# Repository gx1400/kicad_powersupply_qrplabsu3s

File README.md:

# Linear regulator Power supply for QRP Labs Ultimate 3s

Designed in KiCad using NTE1929
PCB fab by OshPark

## Tags
rev1 - First board revision.

## Changelog
2023-01-23: Initial commit, board rev 1 fab'd, assembled, and tested

## To Do
- [ ] clearance between heatsink and fuse clip
- [ ] additional silk screen notes on connectors for connector purpose and polarity
- [ ] change resistors to 0805 SMDs
- [ ] add second NTE1929 for 9V

## Purchased items

### Amazon
- [JST-XH connector kit with crimpers](https://www.amazon.com/gp/product/B07ZHB4BBY)
- [Capacitor kit](https://www.amazon.com/gp/product/B01MSQOX0Q)
- [Resistor kit](https://www.amazon.com/gp/product/B00E3JGGF2)
- [TO220 heatsinks](https://www.amazon.com/gp/product/B078ZXZ1GN)

### Digikey
- [Bourns Inc 3266Y-1-103LF - 10k trimmer pot](https://www.digikey.com/en/products/detail/bourns-inc/3266Y-1-103LF/2535458)
- [SCHURTER Inc. 0752.1242, fuse clips](https://www.digikey.com/en/products/detail/schurter-inc/0752-1242/2644924)
- [Bel Fuse Inc. 5MF 2-R, 2A 5x20mm glass fuse](https://www.digikey.com/en/products/detail/bel-fuse-inc/5MF-2-R/1009036)
- [NTE Electronics, Inc NTE1929, Linear regulator TO-220](https://www.digikey.com/en/products/detail/nte-electronics-inc/NTE1929/11655805)

## License

Shield: [![CC BY-SA 4.0][cc-by-sa-shield]][cc-by-sa]

This work is licensed under a
[Creative Commons Attribution-ShareAlike 4.0 International License][cc-by-sa].

[![CC BY-SA 4.0][cc-by-sa-image]][cc-by-sa]

[cc-by-sa]: http://creativecommons.org/licenses/by-sa/4.0/
[cc-by-sa-image]: https://licensebuttons.net/l/by-sa/4.0/88x31.png
[cc-by-sa-shield]: https://img.shields.io/badge/License-CC%20BY--SA%204.0-lightgrey.svg

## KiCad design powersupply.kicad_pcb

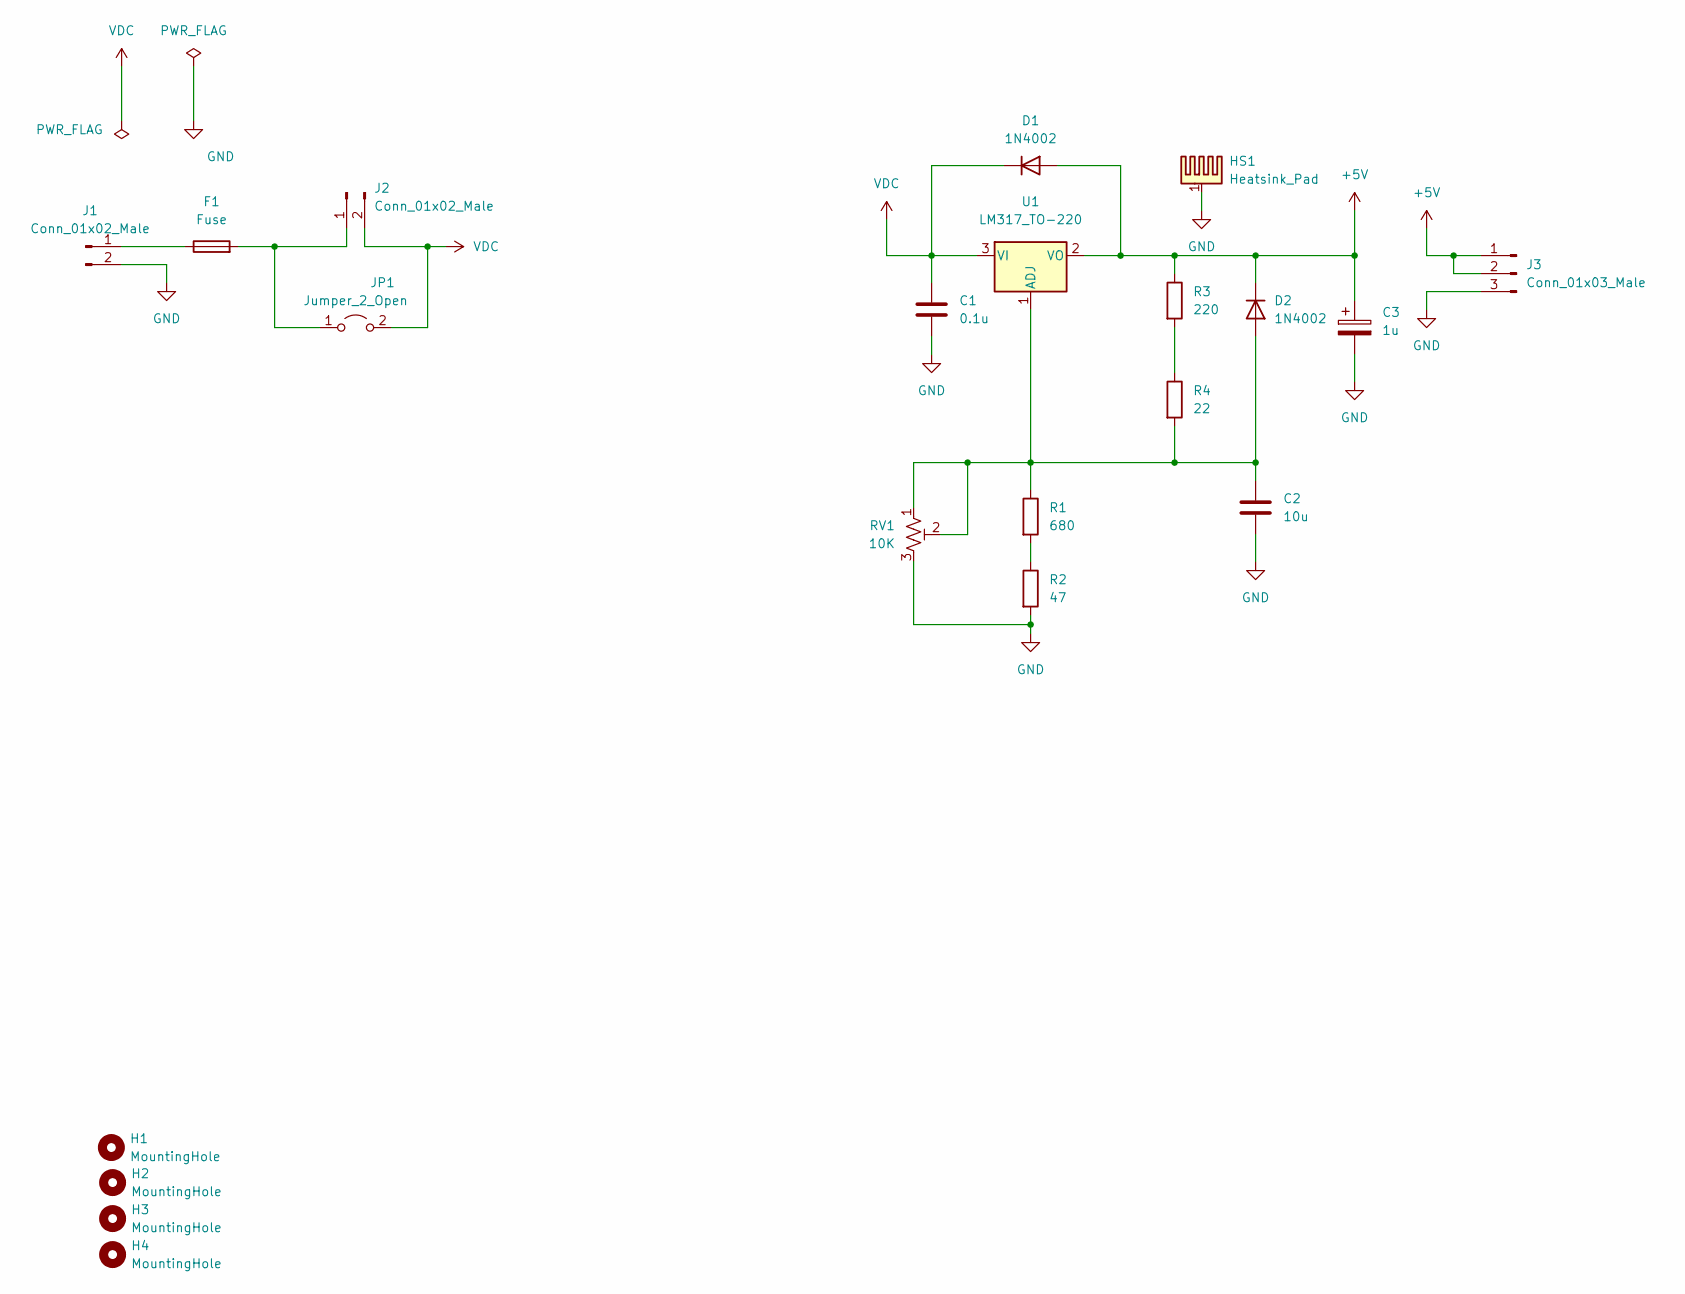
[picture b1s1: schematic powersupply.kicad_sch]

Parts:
C1: 0.1u; CP_Radial_D4.0mm_P2.00mm
C2: 10u; CP_Radial_D5.0mm_P2.00mm
C3: 1u; CP_Radial_D5.0mm_P2.50mm
D1, D2: 1N4002; D_DO-41_SOD81_P10.16mm_Horizontal
F1: Fuse; Fuseholder_Clip-5x20mm_Schurter_CQM_Inline_P20.60x5.00mm_D1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
H1, H2, H3, H4: MountingHole; MountingHole_3.2mm_M3
HS1: Heatsink_Pad; Heatsink_TO-220-3_Vertical_Amazon_B078ZXZ1GN
J1, J2: Conn_01x02_Male; JST_XH_B2B-XH-AM_1x02_P2.50mm_Vertical
J3: Conn_01x03_Male; JST_XH_B3B-XH-A_1x03_P2.50mm_Vertical
JP1: Jumper_2_Open; TestPoint_2Pads_Pitch2.54mm_Drill0.8mm
R1: 680; R_Axial_DIN0207_L6.3mm_D2.5mm_P10.16mm_Horizontal
R2: 47; R_Axial_DIN0207_L6.3mm_D2.5mm_P10.16mm_Horizontal
R3: 220; R_Axial_DIN0207_L6.3mm_D2.5mm_P10.16mm_Horizontal
R4: 22; R_Axial_DIN0207_L6.3mm_D2.5mm_P10.16mm_Horizontal
RV1: 10K; Potentiometer_Bourns_3266Y_Vertical; PartNumber 3266Y-1-103LF
U1: LM317_TO-220; TO-220-3_Vertical

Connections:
+5V: C3.1, D1.2 (A), D2.1 (K), J3.1, J3.2, R3.1, U1.2 (VO)
GND: C1.2, C2.2, C3.2, HS1.1, J1.2, J3.3, R2.2, RV1.3
unnamed: C2.1, D2.2 (A), R1.1, R4.2, RV1.1, RV1.2, U1.1 (ADJ)
unnamed: F1.1, J1.1
unnamed: F1.2, J2.1, JP1.1 (A)
unnamed: R1.2, R2.1
unnamed: R3.2, R4.1
VDC: C1.1, D1.1 (K), J2.2, JP1.2 (B), U1.3 (VI)

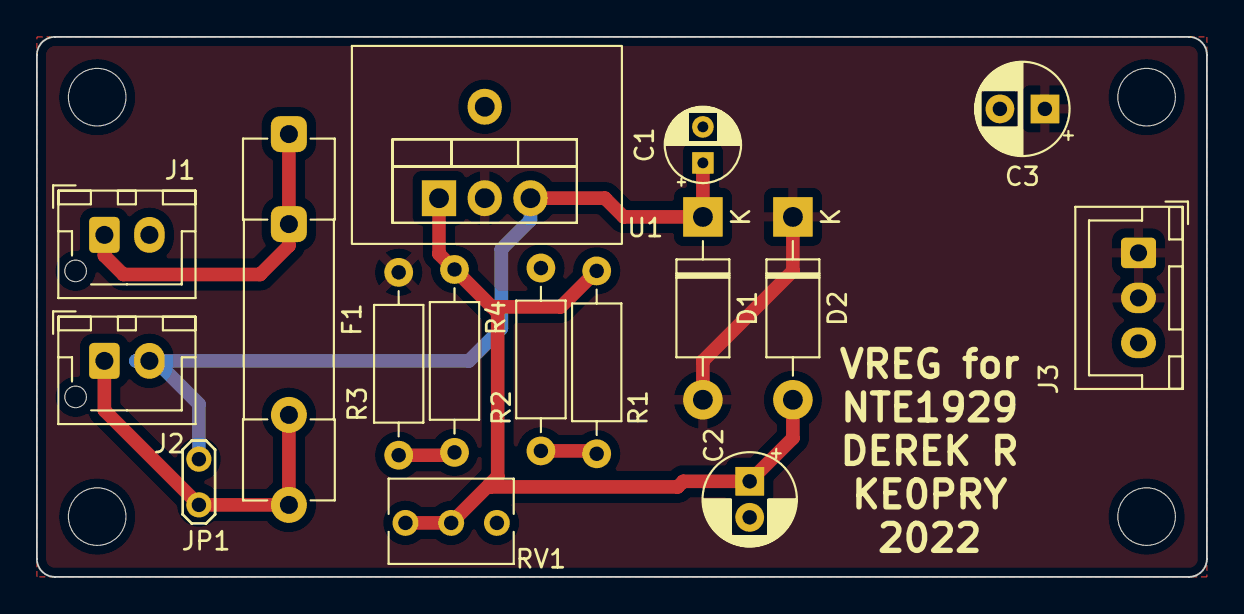
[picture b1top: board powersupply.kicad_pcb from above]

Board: 2 copper layers, 65.0 x 30.0 mm, 21 parts (0 on the bottom side), 8 nets.

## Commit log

2023-01-20 initial commit of board rev1
2023-01-20 add readme
